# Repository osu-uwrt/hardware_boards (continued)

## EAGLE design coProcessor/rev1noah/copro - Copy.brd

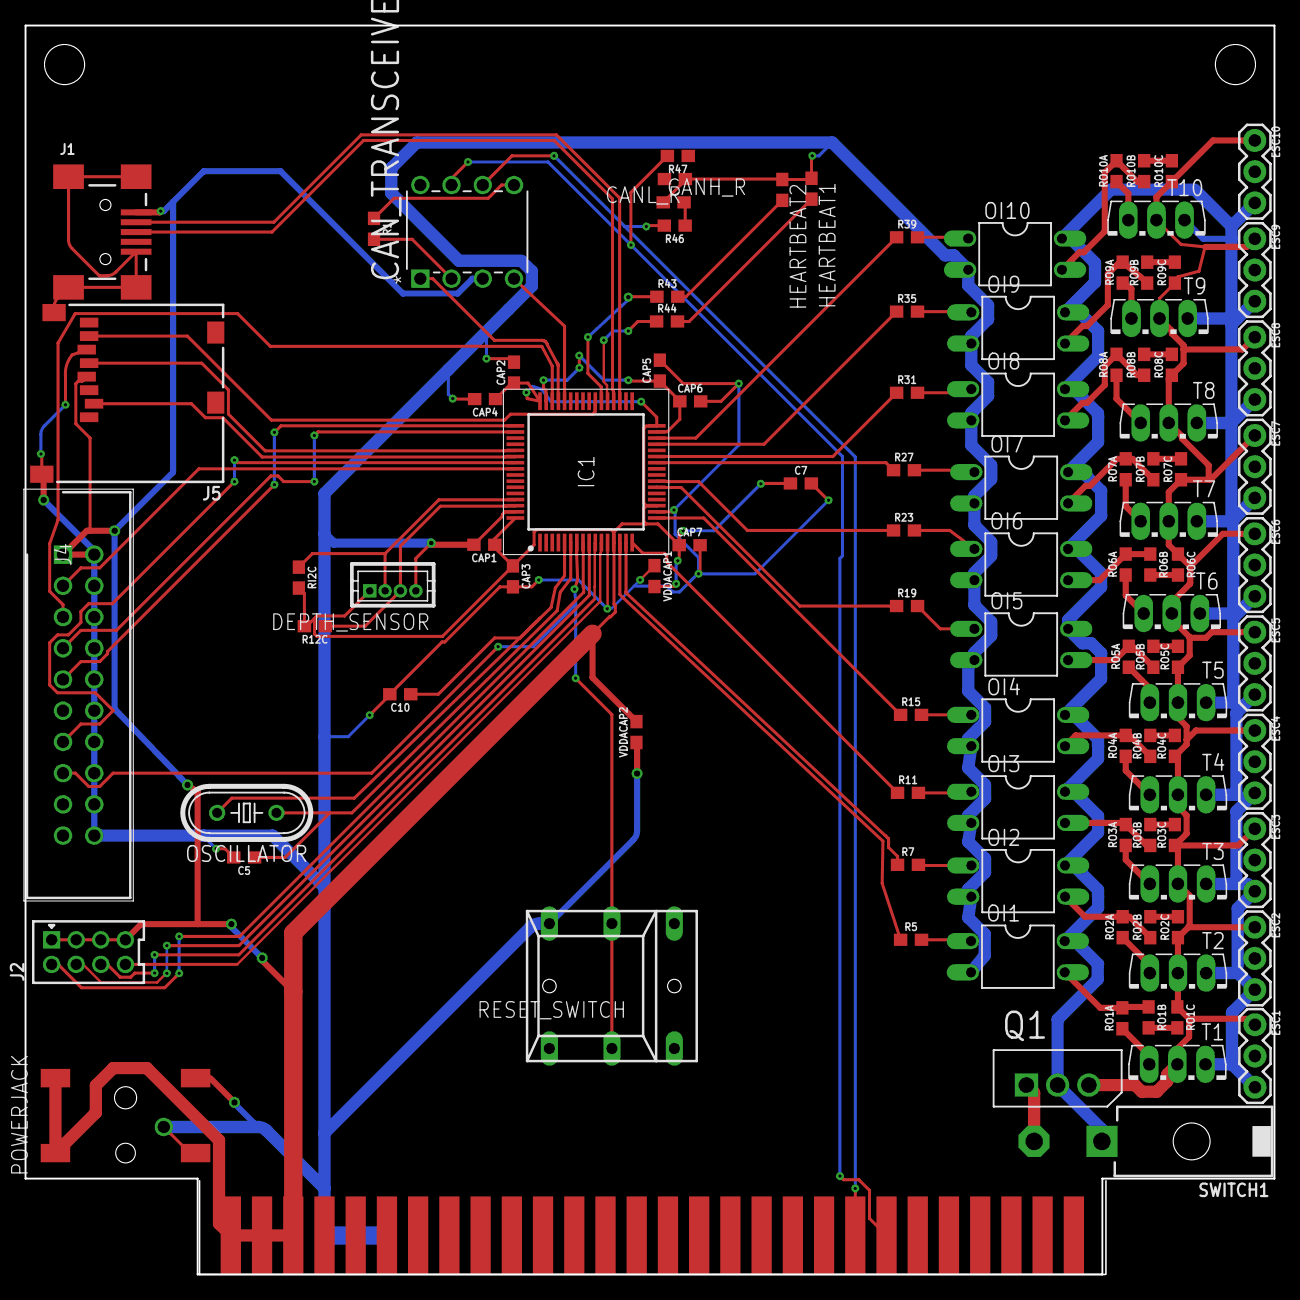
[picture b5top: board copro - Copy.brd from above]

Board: 2 copper layers, 101.6 x 101.6 mm, 106 parts (0 on the bottom side), 88 nets.

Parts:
C5, C10: 1nF; 0603
C7: .1 uF; 0603
CANH_R: LTST-S270GKT; 0603
CANL_R: LTST-S270GKT; 0603
CAN_TRANSCEIVER: MCP2551-I/P; DIP254P762X432-8
CAP1, CAP2, CAP3, CAP4: 100nF; 0603
CAP5, CAP6: 2.2uF; 0603
CAP7: 4.7uF; 0603
DEPTH_SENSOR: DF13-4P-1.25DSA
ESC1, ESC2, ESC3, ESC4, ESC5, ESC6, ESC7, ESC8, ESC9, ESC10: 1X03
HEARTBEAT1, HEARTBEAT2: LTST-S270GKT; 0603
IC1: STM32F405RGT6; QFP50P1200X1200X160-64N
J1: USB_MINI-B_SMT; USB-MINIB
J2: 79107-08
J4: 30320-6002HB; SHDR20W81P254_2X10_3300X840X93
J5: 5008730806
OI1, OI2, OI3, OI4, OI5, OI6, OI7, OI8, OI9, OI10: SFH610; DIL04
OSCILLATOR: HC49/S
POWERJACK: PJ-002AH-SMT-TR; CUI_PJ-002AH-SMT-TR
Q1: L78M05CV; TO254P450X1020X1935-3P
R1, R43, R44, R46, R47: 330; 0603
R5, R7, R11, R15, R19, R23, R27, R31, R35, R39: 220; 0603
R12C: 4.7k; 0603
RESET_SWITCH: REKN
RI2C: 4.7k; 0603
RO1A, RO2A, RO3A, RO4A, RO5A, RO6A, RO7A, RO8A, RO9A, RO10A: 1k; 0603
RO1B, RO1C, RO2B, RO2C, RO3B, RO3C, RO4B, RO4C, RO5B, RO5C, RO6B, RO6C, RO7B, RO7C, RO8B, RO8C, RO9B, RO9C, RO10B, RO10C: 10k; 0603
SWITCH1: 39-30-02?; 39-30-?02?
T1, T2, T3, T4, T5, T6, T7, T8, T9, T10: TO126V
U$1: 5530843; 5530843-6-BOARDFINGERS
VDDACAP1: 100nF; 0603
VDDACAP2: 1uF; 0603

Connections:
2: IC1.8, J2.2
3.3V: C7.1, CAN_TRANSCEIVER.3, CAP1.1, CAP2.1, CAP3.1, CAP4.1, CAP7.1, DEPTH_SENSOR.P$1, IC1.13, IC1.19, IC1.32, IC1.48, IC1.64, J1.VBUS, J2.1, J2.3, J2.5, J2.7, J4.1, J4.2, J5.4, POWERJACK.1.1, POWERJACK.1.2, R12C.2, RI2C.2, U$1.3.3VP1, U$1.3.3VP2, U$1.3.3VP3, VDDACAP1.2, VDDACAP2.2
4: IC1.9, J2.4
5V: ESC1.1, ESC2.1, ESC3.1, ESC4.1, ESC5.1, ESC6.1, ESC7.1, ESC8.1, ESC9.1, ESC10.1, Q1.3, RO1C.1, RO2C.1, RO3C.1, RO4C.1, RO5C.1, RO6C.1, RO7C.1, RO8C.1, RO9C.1, RO10C.1, T1.2, T2.2, T3.2, T4.2, T5.2, T6.2, T7.2, T8.2, T9.2, T10.2
6: IC1.10, J2.6
8: IC1.11, J2.8
18_22V: Q1.1, SWITCH1.2
CANH: CAN_TRANSCEIVER.6, R46.2, U$1.CAN_H
CANL: CAN_TRANSCEIVER.7, R47.2, U$1.CAN_L
CLK: IC1.53, J5.5
CMD: IC1.54, J5.2
D+: IC1.36, J1.D+
D-: IC1.35, J1.D-
DATO: IC1.39, J5.7
GND: C5.2, C7.2, C10.2, CANH_R.1, CANL_R.1, CAP1.2, CAP2.2, CAP3.2, CAP4.2, CAP5.2, CAP6.2, CAP7.2, DEPTH_SENSOR.P$4, HEARTBEAT1.1, HEARTBEAT2.1, IC1.12, IC1.18, IC1.63, J1.GND, J1.S1, J1.S2, J1.S3, J1.S4, J4.4, J4.6, J4.8, J4.10, J4.12, J4.14, J4.16, J4.18, J4.20, J5.6, J5.S3, J5.S4, OI1.2, OI2.2, OI3.2, OI4.2, OI5.2, OI6.2, OI7.2, OI8.2, OI9.2, OI10.2, POWERJACK.2, POWERJACK.3, RESET_SWITCH.0B, U$1.GND1, U$1.GND2, U$1.GND3, U$1.GND_4, U$1.GND_5, U$1.GND_6, VDDACAP1.1, VDDACAP2.1
GNDBAT: ESC1.3, ESC2.3, ESC3.3, ESC4.3, ESC5.3, ESC6.3, ESC7.3, ESC8.3, ESC9.3, ESC10.3, OI1.4, OI2.4, OI3.4, OI4.4, OI5.4, OI6.4, OI7.4, OI8.4, OI9.4, OI10.4, Q1.2, SWITCH1.1, T1.1, T2.1, T3.1, T4.1, T5.1, T6.1, T7.1, T8.1, T9.1, T10.1
HEARTBEAT1: IC1.37, R44.1
HEARTBEAT2: IC1.38, R43.1
JTAG3: IC1.56, J4.3
JTAG5: IC1.46, J4.5
JTAG9: IC1.49, J4.9
JTAG13: IC1.55, J4.13
JTAG15: IC1.7, J4.15, RESET_SWITCH.1A, RESET_SWITCH.1B
unnamed: CAN_TRANSCEIVER.2, R1.2
unnamed: CANL_R.2, R47.1
unnamed: CAN_TRANSCEIVER.5, R1.1
unnamed: HEARTBEAT2.2, R43.2
unnamed: HEARTBEAT1.2, R44.2
unnamed: CANH_R.2, R46.1
OI1: IC1.14, R5.1
OI2: IC1.15, R7.1
OI3: IC1.16, R11.1
OI4: IC1.17, R15.1
OI5: IC1.22, R19.1
OI6: IC1.23, R23.1
OI7: IC1.26, R27.1
OI8: IC1.27, R31.1
OI10: IC1.30, R39.1
OIO9: IC1.29, R35.1
OSC1: C5.1, IC1.6, OSCILLATOR.1
OSC2: C10.1, IC1.5, OSCILLATOR.2
P$2: DEPTH_SENSOR.P$2, IC1.61, RI2C.1
PA15: IC1.50, J4.7
POWER: U$1.3.3V_4, U$1.3.3V_5, U$1.3.3V_6
POWER1O1: RO1B.2, RO1C.2
POWER1O2: RO2B.2, RO2C.2
POWER1O3: RO3B.2, RO3C.2
POWER1O4: RO4B.2, RO4C.2
POWER1O5: RO5B.2, RO5C.2
POWER1O6: RO6B.2, RO6C.2
POWER1O7: RO7B.2, RO7C.2
POWER1O8: RO8B.2, RO8C.2
POWER1O9: RO9B.2, RO9C.2
POWER1O10: RO10B.2, RO10C.2
POWER2O1: OI1.3, RO1A.2, RO1B.1
POWER2O2: OI2.3, RO2A.2, RO2B.1
POWER2O3: OI3.3, RO3A.2, RO3B.1
POWER2O4: OI4.3, RO4A.2, RO4B.1
POWER2O5: OI5.3, RO5A.2, RO5B.1
POWER2O6: OI6.3, RO6A.2, RO6B.1
POWER2O9: OI9.3, RO9A.2, RO9B.1
POWER2O10: OI10.3, RO10A.2, RO10B.1
POWER207: OI7.3, RO7A.2, RO7B.1
POWER208: OI8.3, RO8A.2, RO8B.1
PS$3: DEPTH_SENSOR.P$3, IC1.62, R12C.1
PWM1: OI1.1, R5.2
PWM2: OI2.1, R7.2
PWM3: OI3.1, R11.2
PWM4: OI4.1, R15.2
PWM5: OI5.1, R19.2
PWM6: OI6.1, R23.2
PWM7: OI7.1, R27.2
PWM8: OI8.1, R31.2
PWM9: OI9.1, R35.2
PWM10: OI10.1, R39.2
RXD: CAN_TRANSCEIVER.4, IC1.44
T1: RO1A.1, T1.3
T2: RO2A.1, T2.3
T3: RO3A.1, T3.3
T4: RO4A.1, T4.3
T5: RO5A.1, T5.3
T6: RO6A.1, T6.3
T7: RO7A.1, T7.3
T8: RO8A.1, T8.3
T9: RO9A.1, T9.3
T10: RO10A.1, T10.3
TXD: CAN_TRANSCEIVER.1, IC1.45
VCAP_2TO1: CAP5.1, CAP6.1, IC1.31, IC1.47
